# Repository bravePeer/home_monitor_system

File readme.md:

# Home Monitor System
This project idea is to gather environmental information around the home.

In principle, sensors send data to a receiver, which is connected to a server.

General flow
```
Sensor ---> Bridge ---> Server
```

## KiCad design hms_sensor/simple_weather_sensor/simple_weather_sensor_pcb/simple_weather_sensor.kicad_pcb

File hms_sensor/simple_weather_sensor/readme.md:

## Schematic of Simple Weather Sensor

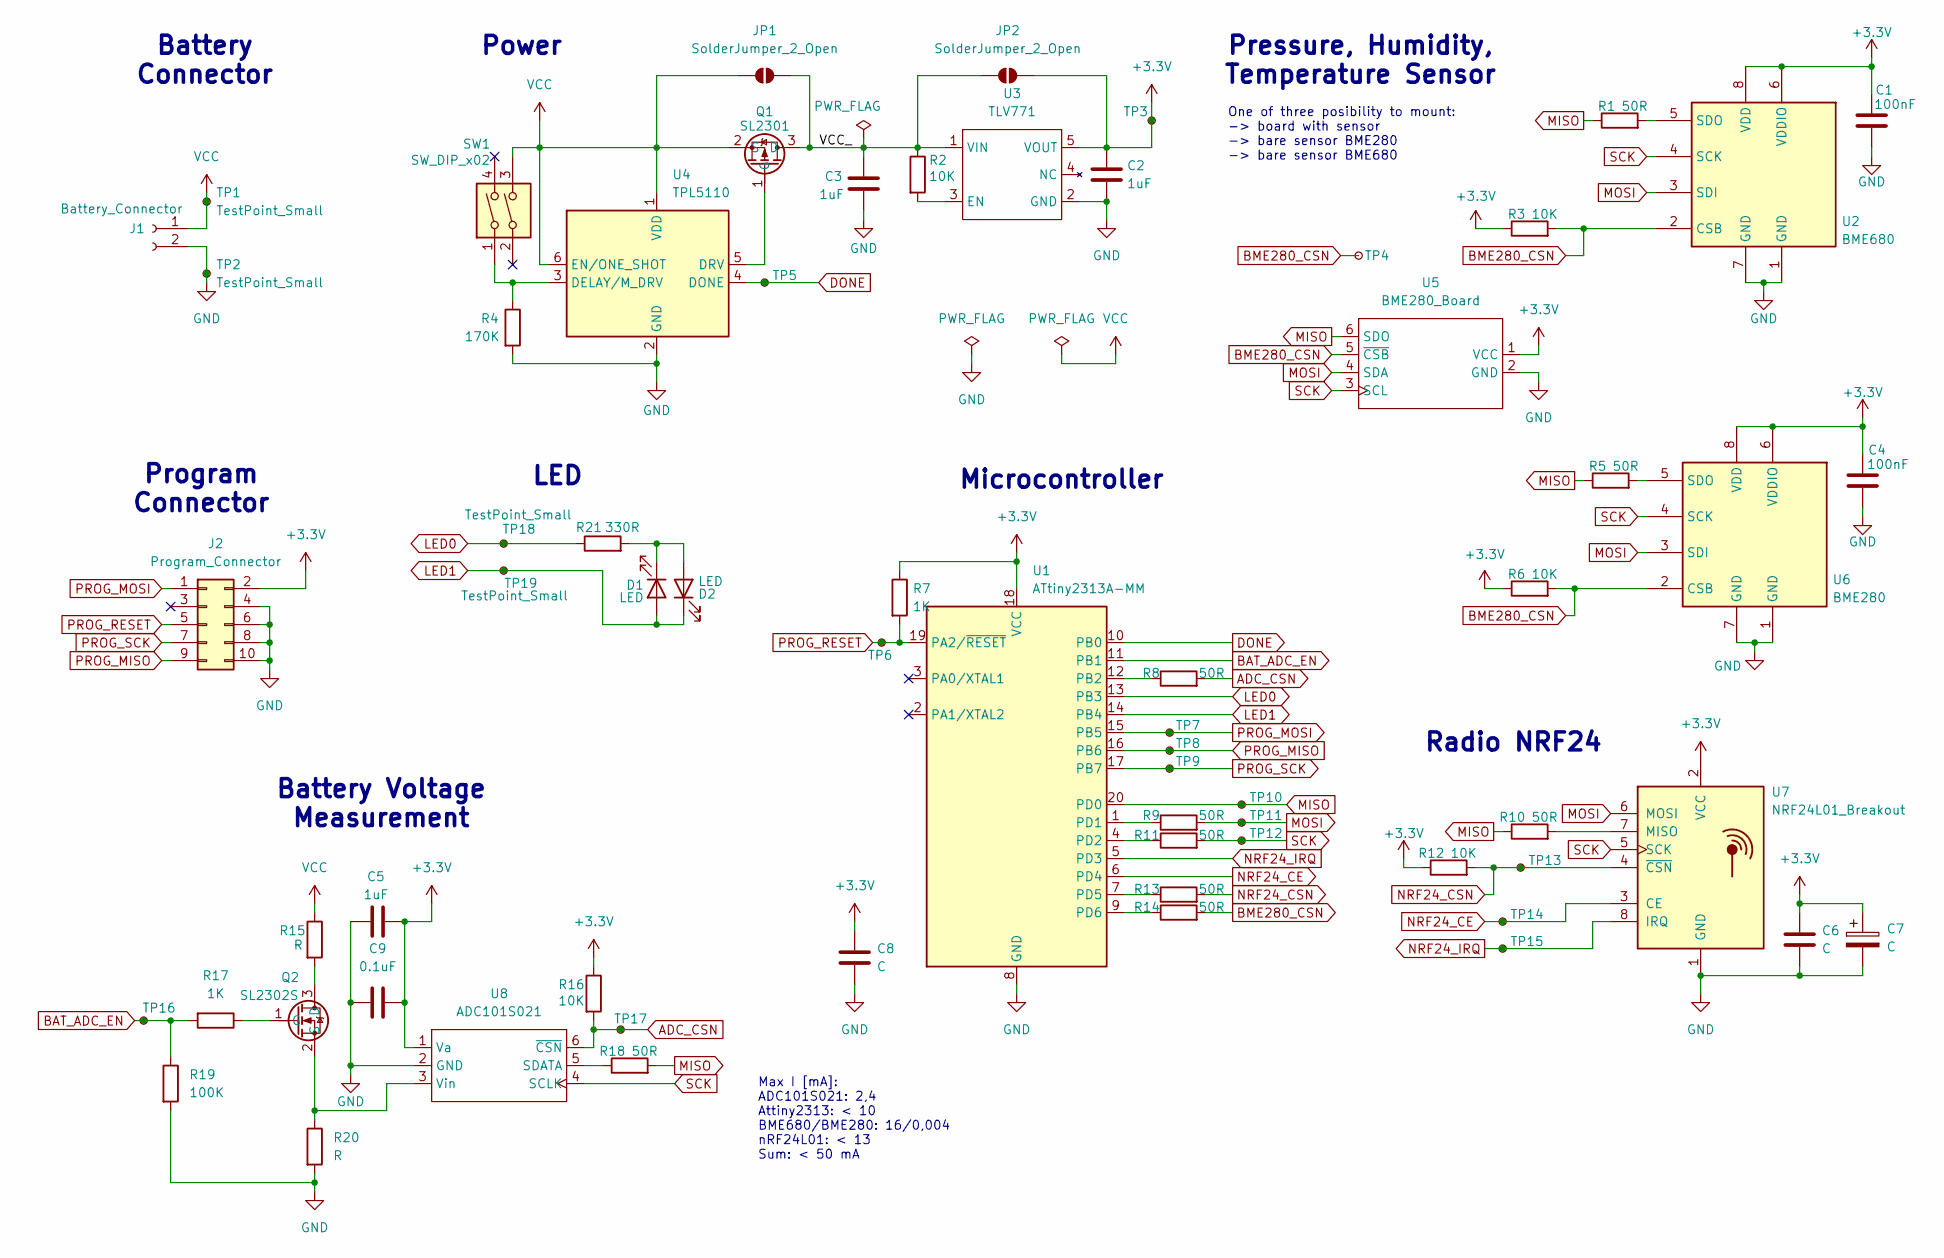
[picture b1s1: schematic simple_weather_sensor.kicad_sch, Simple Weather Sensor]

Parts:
C1, C4: 100nF; C_0805_2012Metric
C2, C3, C5: 1uF; C_0805_2012Metric
C6, C8: C; C_0805_2012Metric
C7: C; C_1210_3225Metric
C9: 0.1uF; C_0805_2012Metric
D1, D2: LED; D_0603_1608Metric
J1: Battery_Connector; PinHeader_1x02_P2.54mm_Vertical
J2: Program_Connector; PinHeader_2x05_P2.54mm_Vertical
JP1, JP2: SolderJumper_2_Open; SolderJumper-2_P1.3mm_Open_Pad1.0x1.5mm
Q1: SL2301; SOT-23
Q2: SL2302S; SOT-23
R1, R5, R8, R9, R10, R11, R13, R14, R18: 50R; R_0805_2012Metric
R2, R3, R6, R12, R16: 10K; R_0805_2012Metric
R4: 170K; R_0805_2012Metric
R7, R17: 1K; R_0805_2012Metric
R15, R20: R; R_0805_2012Metric
R19: 100K; R_0805_2012Metric
R21: 330R; R_0805_2012Metric
SW1: SW_DIP_x02; SW_Push_2P1T_Toggle_CK_PVA1xxH4xxxxxxV2
TP1, TP2, TP3, TP18, TP19: TestPoint_Small; TestPoint_Pad_D1.0mm
TP4, TP5, TP6, TP7, TP8, TP9, TP10, TP11, TP12, TP13, TP14, TP15, TP16, TP17: TestPoint_Pad_D1.0mm
U1: ATtiny2313A-MM; VQFN-20-1EP_3x3mm_P0.45mm_EP1.55x1.55mm
U2: BME680; Bosch_LGA-8_3x3mm_P0.8mm_ClockwisePinNumbering
U3: TLV771; SOT-23-5
U4: TPL5110; SOT-23-6
U5: BME280_Board; PinHeader_1x06_P2.54mm_Vertical
U6: BME280; Bosch_LGA-8_2.5x2.5mm_P0.65mm_ClockwisePinNumbering
U7: NRF24L01_Breakout; nRF24L01_Breakout
U8: ADC101S021; SOT-23-6

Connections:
+3.3V: C1.2, C2.2, C4.2, C5.1, C6.1, C7.1, C8.1, C9.2, J2.2, JP2.2 (B), R3.1, R6.1, R7.1, R12.1, R16.1, TP3.1, U1.18 (VCC), U2.6 (VDDIO), U2.8 (VDD), U3.5 (VOUT), U5.1 (VCC), U6.6 (VDDIO), U6.8 (VDD), U7.2 (VCC), U8.1 (Va)
/VCC_: C3.2, JP1.2 (B), JP2.1 (A), Q1.3 (D), R2.1, U3.1 (VIN)
ADC_CSN: R8.2, R16.2, TP17.1, U8.6 (~CSN)
BAT_ADC_EN: R17.2, R19.1, TP16.1, U1.11 (PB1)
BME280_CSN: R3.2, R6.2, R14.2, TP4.1, U2.2 (CSB), U5.5 (~CSB), U6.2 (CSB)
DONE: TP5.1, U1.10 (PB0), U4.4 (DONE)
GND: C1.1, C2.1, C3.1, C4.1, C5.2, C6.2, C7.2, C8.2, C9.1, J1.2, J2.4, J2.6, J2.8, J2.10, R4.2, R19.2, R20.2, TP2.1, U1.8 (GND), U1.21 (GND), U2.1 (GND), U2.7 (GND), U3.2 (GND), U4.2 (GND), U5.2 (GND), U6.1 (GND), U6.7 (GND), U7.1 (GND), U8.2 (GND)
LED0: R21.1, TP18.1, U1.13 (PB3)
LED1: D1.2 (A), D2.1 (K), TP19.1, U1.14 (PB4)
MISO: R1.1, R5.1, R10.1, R18.2, TP10.1, U1.20 (PD0), U5.6 (SDO)
MOSI: R9.2, TP11.1, U2.3 (SDI), U5.4 (SDA), U6.3 (SDI), U7.6 (MOSI)
NRF24_CE: TP14.1, U1.6 (PD4), U7.3 (CE)
NRF24_CSN: R12.2, R13.2, TP13.1, U7.4 (~CSN)
NRF24_IRQ: TP15.1, U1.5 (PD3), U7.8 (IRQ)
unnamed: D1.1 (K), D2.2 (A), R21.2
unnamed: Q1.1 (G), U4.5 (DRV)
unnamed: Q2.3 (D), R15.2
unnamed: Q2.1 (G), R17.1
unnamed: Q2.2 (S), R20.1, U8.3 (Vin)
unnamed: R8.1, U1.12 (PB2)
unnamed: R9.1, U1.1 (PD1)
unnamed: R11.1, U1.4 (PD2)
unnamed: R13.1, U1.7 (PD5)
unnamed: R14.1, U1.9 (PD6)
unnamed: R1.2, U2.5 (SDO)
unnamed: R2.2, U3.3 (EN)
unnamed: R4.1, SW1.1, U4.3 (DELAY/M_DRV)
unnamed: R5.2, U6.5 (SDO)
unnamed: R10.2, U7.7 (MISO)
unnamed: R18.1, U8.5 (SDATA)
PROG_MISO: J2.9, TP8.1, U1.16 (PB6)
PROG_MOSI: J2.1, TP7.1, U1.15 (PB5)
PROG_RESET: J2.5, R7.2, TP6.1, U1.19 (PA2/~RESET)
PROG_SCK: J2.7, TP9.1, U1.17 (PB7)
SCK: R11.2, TP12.1, U2.4 (SCK), U5.3 (SCL), U6.4 (SCK), U7.5 (SCK), U8.4 (SCLK)
VCC: J1.1, JP1.1 (A), Q1.2 (S), R15.1, SW1.3, TP1.1, U4.1 (VDD), U4.6 (EN/ONE_SHOT)

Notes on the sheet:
Battery Voltage Measurement
Battery Connector
Program Connector
Max I [mA]: ADC101S021: 2,4 Attiny2313: < 10 BME680/BME280: 16/0,004 nRF24L01: < 13 Sum: < 50 mA
Microcontroller
Radio NRF24
One of three posibility to mount: -> board with sensor -> bare sensor BME280 -> bare sensor BME680
Pressure, Humidity, Temperature Sensor
LED
Power

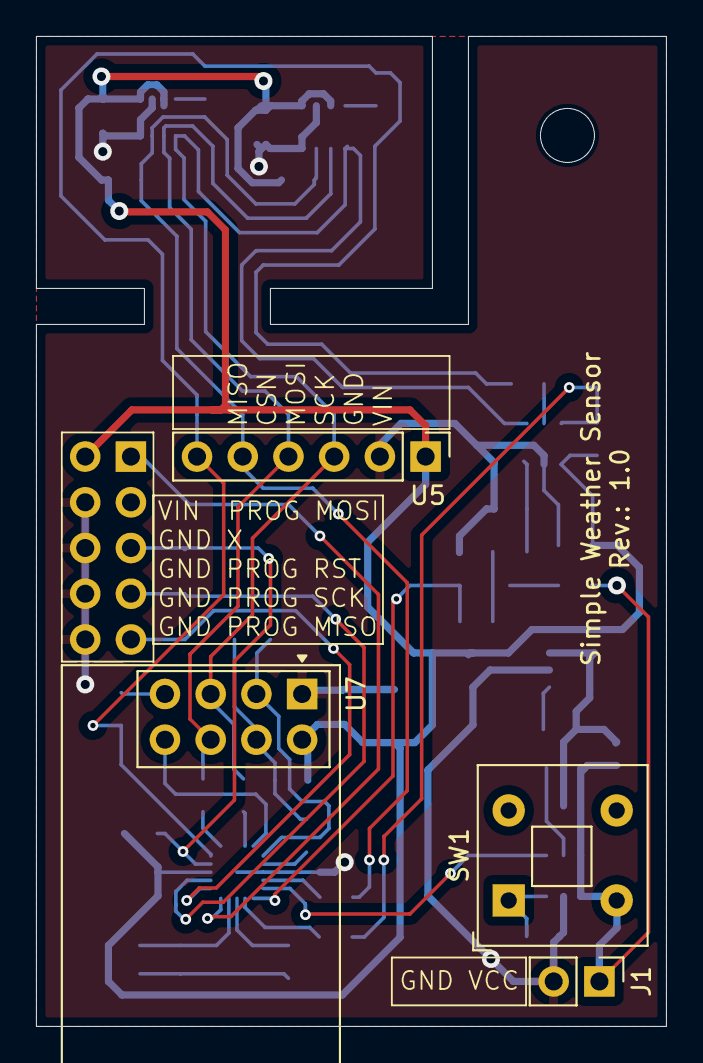
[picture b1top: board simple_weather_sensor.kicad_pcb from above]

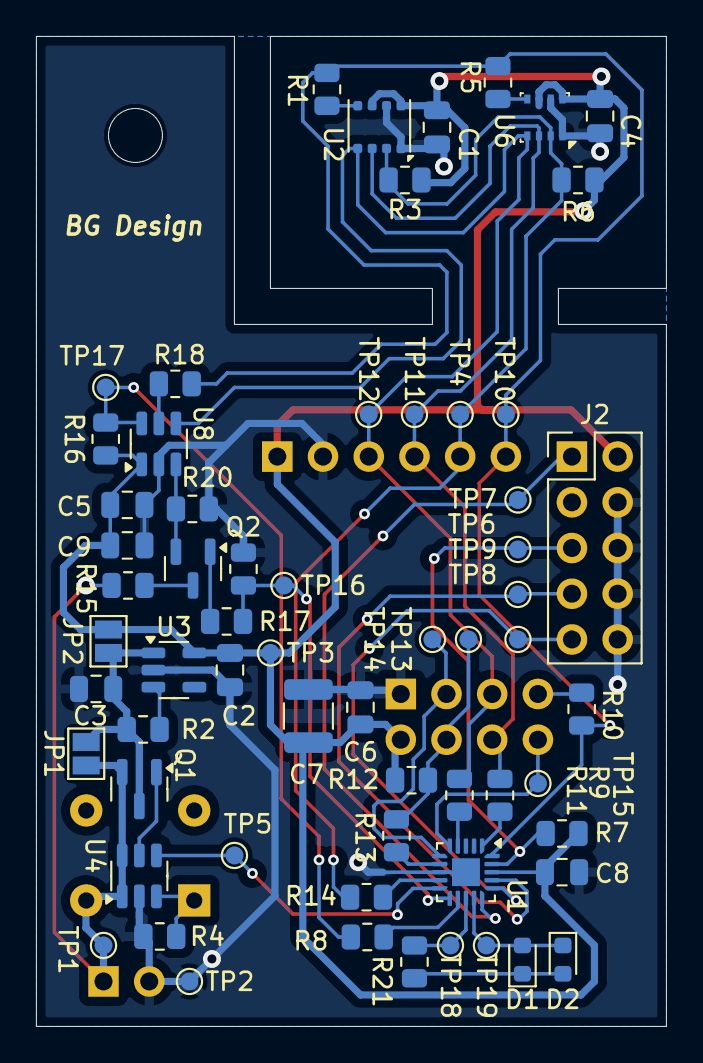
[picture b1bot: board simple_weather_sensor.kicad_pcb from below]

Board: 2 copper layers, 35.0 x 55.0 mm, 66 parts (62 on the bottom side), 36 nets.

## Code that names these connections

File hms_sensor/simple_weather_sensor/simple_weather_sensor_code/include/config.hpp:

#pragma once
#ifdef ATTINY2313A
#include <stdint.h>
extern "C"
{
    #include "avr/io.h"
    #include "avr/interrupt.h"
    #include "avr/sleep.h"
    #include "util/delay.h"
}
#include "spi.hpp"

const portType BME_CSN_PORT = &PORTD;
const pinType BME_CSN_PIN = PD6;

const portType NRF24_CSN_PORT = &PORTD;
const pinType NRF24_CSN_PIN = PD5;
inline portType NRF24_CE_PORT = &PORTD;
inline pinType NRF24_CE_PIN = PD4;
const portType NRF24_IRQ_PORT = &PORTD;
const pinType NRF24_IRQ_PIN = PD3;


const portType donePort = &PORTB;
const pinType donePin = PB0;

const portType batteryVoltageEnablePort = &PORTB;
const pinType batteryVoltageEnablePin = PB1;
const portType batteryVoltageCsnPort = &PORTB;
const pinType batteryVoltageCsnPin = PB2;

const portType ledDir = &DDRB;
const portType ledPort = &PORTB;
const pinType ledPin0 = PB4;
const pinType ledPin1 = PB3;

const portType buttonPort = &PORTB;
constexpr uint8_t buttonRightPin = PB5;
constexpr uint8_t buttonLeftPin = PB6;

constexpr pinType progMosi = PB5;
constexpr pinType progMiso = PB6;
constexpr pinType progClk = PB7;

/// @brief Initialize uC and ports
inline void init()
{
    DDRB = (1 << ledPin0) 
        | (1 << ledPin1) 
        | (1 << batteryVoltageEnablePin) 
        | (1 << batteryVoltageCsnPin)
        | (1 << donePin)
#if !defined(NO_SLEEP_TIMER)
        | (1 << progMosi)
        | (0 << progMiso)
        | (1 << progClk)
#endif
        ;

    PORTB = (1 << batteryVoltageCsnPin) 
        | (1 << ledPin0) 
        | (1 << ledPin1) 
#if defined(NO_SLEEP_TIMER)
        | (1 << buttonRightPin) 
        | (1 << buttonLeftPin)
#else
        | (1 << progMosi)
        | (0 << progMiso)
        | (1 << progClk)
#endif
        ;

    DDRD = (1 << NRF24_CSN_PIN) | (1 << NRF24_CE_PIN) | (1 << BME_CSN_PIN);
    PORTD = (1 << NRF24_CSN_PIN) | (1 << NRF24_CE_PIN) | (1 << BME_CSN_PIN);
    
    // MCUCR |= (1<<SE); // Enable sleep is set before go sleep
    MCUCR = (1 << ISC11) // Set falling edgne on INT1 (irqPin)
    | (1<<SM1) | (1<<SM0); // Configure sleep mode to Power Down
    
    // Config interrupt
    GIFR = 0xf4;
    GIMSK = (1 << INT1); // Enable INT1 interrupt

    // Disable ADC
    ACSR |= (1 << ACD);
}

#endif

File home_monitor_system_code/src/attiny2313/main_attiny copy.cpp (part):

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// }
// #include "spi.h"

// #define NRF24_CSN_PORT PORTD
// #define NRF24_CSN_PIN (uint8_t)PD4
// #define NRF24_CE_PORT PORTD
// #define NRF24_CE_PIN (uint8_t)PD5
// #define NRF24_IRQ_PORT PORTD
// #define NRF24_IRQ_PIN (uint8_t)PD3
// #define DELAY_MS(val) _delay_ms(val)
// #define DELAY_US(val) _delay_us(val)
// #include "nRF24.h"
// #define BME280_CSN_PORT PORTD
// #define BME280_CSN_PIN (uint8_t)PD6
// #include "bme280.h"
// #include "nRF24Data.h"
// // Attiny2313 -> gdy uśpione 18 uA
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

// #ifdef ATTINY2313A
// constexpr uint8_t buttonRightPin = PB0;
// constexpr uint8_t buttonLeftPin = PB1;
// constexpr uint8_t ledPIN0 = PB2;
// constexpr uint8_t ledPIN1 = PB3;
// #define LED_DDR DDRB
// #define LED_PORT PORTB

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
// void setDone()
// {
//   PORTD |= (1<<PD6);
//   _delay_ms(1);
//   PORTD &= ~(1<<PD6);
//   _delay_ms(1);
// }

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// {
//   state = State::Idle;

//   NRF24_CE_PORT &= ~(1<<NRF24_CE_PIN);
//   // _delay_us(1);
//   uint8_t status = transmitSPI(nullptr, nullptr, WriteCmd(Commands::Nop), 0, &NRF24_CSN_PORT, NRF24_CSN_PIN);
  
  
//   switch (status & SetRegister(Reg::Status::max_rt, Reg::Status::tx_ds, Reg::Status::rx_dr))
//   {
//     case SetRegister(Reg::Status::rx_dr): // Data ready, received data
//       transmitSPI(&dataCoutToProcess, &dataCoutToProcess, WriteCmd(Commands::ReadRxPayloadWidth), 1, &NRF24_CSN_PORT, NRF24_CSN_PIN);
//       // dataCoutToProcess = dataToProcess[0];
      
//       transmitSPI(dataToProcess, dataToProcess, WriteCmd(Commands::ReadRxPayload), dataCoutToProcess, &NRF24_CSN_PORT, NRF24_CSN_PIN);
//       shouldSend = 1;
//       break;
//     case SetRegister(Reg::Status::max_rt):
//       transmitSPI(nullptr, nullptr, WriteCmd(Commands::FlushTx), 0, &NRF24_CSN_PORT, NRF24_CSN_PIN);
//       turnOnRedLed();
//       break;
//     case SetRegister(Reg::Status::tx_ds):
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//   }

//   uint8_t resetReg = 0x70;
//   transmitSPI(&resetReg, &resetReg, WriteRegister(RegMap::Status), 1, &NRF24_CSN_PORT, NRF24_CSN_PIN);
//   NRF24_CE_PORT |= (1<<NRF24_CE_PIN);
// }

// volatile uint8_t timerCounter = 0;
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// int main()
// {
//   // Testing TPL
//   // DDRD |= (1<<PD6);
// //   PORTD = 0;
//   //
// //   DDRB = 0x00;
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//   //
// //   intSPI(1000u);
// //   DDRD |= (1<<csnPIN);
// //   DDRD |= (1<<PD6);
//   //
// //   PORTD |= (1<<PD6);
// //
// //   DDRD &= ~(1<<NRF24_IRQ_PIN);
// //   DDRD |= (1<<NRF24_CE_PIN);
// //   nrf24::initnRF24(); // nrf is in PRX
// //
// //   uint8_t dd = 0;
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// //   nrf24::setToPTX();
// //   uint8_t sendBuf2[5] = {'a', 'b', 'c', 'd', 'e'};
// //   nrf24::sendData(sendBuf2, 5);
// //   NRF24_CE_PORT |= (1<<NRF24_CE_PIN); 
// //   _delay_ms(5000);
// //   while (1)
// //   {
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// //         nrf24::setToPTX();
// //         uint8_t sendBuf3[5] = {'a', 'b', 'c', 'd', 'e'};
// //         nrf24::sendData(sendBuf3, 5);
// //         NRF24_CE_PORT |= (1<<NRF24_CE_PIN); 
// //         _delay_ms(500);
// //         NRF24_CE_PORT &= ~(1<<NRF24_CE_PIN); 
// //         nrf24::setToPRX();
// //         NRF24_CE_PORT |= (1<<NRF24_CE_PIN); // Receiving mode
// //         turnOnGreenLed();
// //         _delay_ms(1000);
// //         turnOffLeds();
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//   LED_DDR |= (1 << ledPIN0) | (1 << ledPIN1);
//   PORTB = (1<<buttonLeftPin) | (1<<buttonRightPin);

//   DDRD |= (1<<NRF24_CSN_PIN) | (1<<NRF24_CE_PIN);
//   NRF24_CSN_PORT |= (1<<NRF24_CSN_PIN);

//   // Config interrupt
//   MCUCR = (1<<ISC11); // Set falling edgne on INT1 (irqPin)
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//   uint8_t data = 1;
//   // uint8_t receivedBuf[5];
//   // uint8_t sendBuf[5] = {0x12, 0x23, 0x61, 0xdd, 0xab};
//   // NRF24_CE_PORT |= (1<<NRF24_CE_PIN); // Active
//   // set_sleep_mode(SLEEP_MODE_PWR_DOWN);

//   //init timer interrupt
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//   sei();
//   // Power down
//   // dd = 0;
//   // transmitSPI(&dd, &dd, ReadRegister(RegMap::Config), 1, &NRF24_CSN_PORT, NRF24_CSN_PIN);
//   // dd &= ~SetRegister(Reg::Config::pwr_up);
//   // transmitSPI(&dd, &dd, WriteRegister(RegMap::Config), 1, &NRF24_CSN_PORT, NRF24_CSN_PIN);

  

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
//       data++;
//       nrf24::setToPRX();
//       NRF24_CE_PORT |= (1<<NRF24_CE_PIN); // Receiving mode
    
//       break;    
//     }
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// #include "usart.h"

// //DDRD
// constexpr uint8_t ledPIN = PD2;
// //DDRD
// constexpr uint8_t buttonLeftPin = PD4;

// // void turnOffLeds()
// // {
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
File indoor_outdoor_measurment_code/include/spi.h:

#pragma once
#include <stdint.h>

void intSPI(uint_fast16_t baud);

template <typename T, typename K>
uint8_t simpletransmitSPI(uint8_t cData, T csPort, K csPin);

uint8_t transmitSPI_New(uint8_t* sendBuf, uint8_t* receiveBuf, uint8_t cmd, uint8_t len);

template <typename K, typename T>
uint8_t transmitSPI(uint8_t* sendBuf, uint8_t* receiveBuf, uint8_t cmd, uint8_t len, K csnPort, T csnPin)
{
  *csnPort &= (~(1<<csnPin));
  uint8_t ret = transmitSPI_New(sendBuf, receiveBuf, cmd, len);
  *csnPort |= (1<<csnPin);
  return ret;
}


#if defined(ATTINY2313A)
extern "C" 
{
  #include "avr/io.h"
  #include "util/delay.h"
}


constexpr uint8_t misoPin = PD0;
constexpr uint8_t mosiPin = PD1;
constexpr uint8_t sckPin = PD2;
constexpr uint8_t csnPIN = PD4;

// extern volatile uint8_t misoPort;
// extern volatile uint8_t csnPort;

// uint8_t simpletransmitSPI(uint8_t cData, uint8_t csPin)

inline uint8_t receiveSPIcmd(uint8_t* receiveBuf, uint8_t cmd, uint8_t len)
{
  PORTD &= ~(1<<csnPIN);
  while ( !( UCSRA & (1<<UDRE)) );/* Wait for empty transmit buffer */
  UDR = cmd;
  while ( !(UCSRA & (1<<RXC)) ); /* Wait for data to be received */
  uint8_t statusReg = UDR;

  for (uint8_t i = 0; i < len - 1; i++)
  {
    while ( !( UCSRA & (1<<UDRE)) );/* Wait for empty transmit buffer */
    UDR = 0xff;
    while ( !(UCSRA & (1<<RXC)) ); /* Wait for data to be received */
    receiveBuf[i] = UDR;
  }
  
  PORTD |= (1<<csnPIN);

  return statusReg;
}

inline uint8_t receiveSPIcmd(uint8_t* receiveBuf, uint8_t cmd, uint8_t len, volatile uint8_t csPort, uint8_t csPin)
{
  PORTD &= ~(1<<csPin);
  // csPort &= ~(1<<csPin);
  while ( !( UCSRA & (1<<UDRE)) );/* Wait for empty transmit buffer */
  UDR = cmd;
  while ( !(UCSRA & (1<<RXC)) ); /* Wait for data to be received */
  uint8_t statusReg = UDR;

  for (uint8_t i = 0; i < len - 1; i++)
  {
    while ( !( UCSRA & (1<<UDRE)) );/* Wait for empty transmit buffer */
    UDR = 0xff;
    while ( !(UCSRA & (1<<RXC)) ); /* Wait for data to be received */
    receiveBuf[i] = UDR;
  }
  
  // csPort |= (1<<csPin);
  PORTD |= (1<<csPin);

  return statusReg;
}

inline uint8_t sendSPIcmd(uint8_t* sendBuf, uint8_t cmd, uint8_t len)
{
  PORTD &= ~(1<<csnPIN);
  while ( !( UCSRA & (1<<UDRE)) );/* Wait for empty transmit buffer */
  UDR = cmd;
  while ( !(UCSRA & (1<<RXC)) ); /* Wait for data to be received */
  uint8_t statusReg = UDR;

  for (uint8_t i = 0; i < len - 1; i++)
  {
    while ( !( UCSRA & (1<<UDRE)) );/* Wait for empty transmit buffer */
    UDR = sendBuf[i];
    while ( !(UCSRA & (1<<RXC)) ); /* Wait for data to be received */
    statusReg = UDR;
  }
  
  PORTD |= (1<<csnPIN);

  return statusReg;
}

inline uint8_t sendSPIcmd(uint8_t* sendBuf, uint8_t cmd, uint8_t len, volatile uint8_t* csPort, uint8_t csPin)
{
  *csPort &= ~(1<<csPin);
  while ( !( UCSRA & (1<<UDRE)) );/* Wait for empty transmit buffer */
  UDR = cmd;
  while ( !(UCSRA & (1<<RXC)) ); /* Wait for data to be received */
  uint8_t statusReg = UDR;

  for (uint8_t i = 0; i < len - 1; i++)
  {
    while ( !( UCSRA & (1<<UDRE)) );/* Wait for empty transmit buffer */
    UDR = sendBuf[i];
    while ( !(UCSRA & (1<<RXC)) ); /* Wait for data to be received */
    statusReg = UDR;
  }
  
  *csPort |= (1<<csPin);

  return statusReg;
}



#elif defined(ATMEGA328P)
//DDRB
constexpr uint8_t misoPin = PB4;
//DDRB
constexpr uint8_t mosiPin = PB3;
//DDRB
constexpr uint8_t sckPin = PB5;
//DDRB
constexpr uint8_t csnPIN = PB2;

void initSPI()
{
  /* Set MOSI and SCK output, all others input */
  DDRB |= (1<<mosiPin)|(1<<sckPin)|(1<<csnPIN);
  DDRB &= ~(1<<misoPin);
  PORTD |= (1<<csnPIN);
  
  /* Enable SPI, Master, set clock rate fck/16 */
  SPCR = (1<<SPE)|(1<<MSTR)|(1<<SPR0);
}

void simpletransmitSPI(uint8_t data)
{
  PORTB &= ~(1<<csnPIN);
  /* Start transmission */
  SPDR = data;
  /* Wait for transmission complete */
  while(!(SPSR & (1<<SPIF)));
  PORTB |= (1<<csnPIN);
}

uint8_t transmitSPI(uint8_t* sendBuf, uint8_t* receiveBuf, uint8_t cmd, uint8_t len)
{
  //Enable
  PORTB &= ~(1<<csnPIN);

  SPDR = cmd;
  while(!(SPSR & (1<<SPIF))); /* Wait for data to be received */
  uint8_t statusReg = SPDR;

  for (uint8_t i = 0; i < len; i++)
  {
    SPDR = sendBuf[i];
    while(!(SPSR & (1<<SPIF))); /* Wait for data to be received */
    receiveBuf[i] = SPDR;
  }
  
  //Disable
  PORTB |= (1<<csnPIN);
  _delay_ms(5);
  return statusReg;
}


#endif

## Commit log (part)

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2025-02-04 Add microcontrollers code
2025-02-04 Add readme
2025-02-04 Add gitignore
2025-02-04 Remove .vscode
2025-02-05 Add list and fix native tests
2025-02-06 Update list and add sensor tests
2025-02-06 Add PC app
2025-02-28 Change folder name
2025-02-28 Add schematic to Simple Weather Sensor
2025-03-09 Clean up and update attiny sensor code
2025-03-09 Fix packet len in attiny sensor and remove unnecessary filse
2025-03-18 Add sensor files and commands to debug
2025-03-22 Add reading sensor temperature and pressure
2025-03-22 Split to diffrent files
2025-05-28 Add simple deamon, add docker compose and move files
2025-06-02 Add sensor_menager and update deamon
2025-06-02 Refactor code structure for improved readability and maintainability
2025-06-14 Attiny2313: Add data in EEPROM and split code into files
2025-06-14 Remove Atmega328p and modify Attiny2313A config
2025-06-14 Change send delay and remove blink info
2025-07-21 Update BME lib
2025-07-21 Add check connection to nrf24 lib
2025-07-21 Move files and update
2025-07-24 Add work done
2025-07-24 Change packet structure and add packet types
2025-07-24 Update Attiny2313 config and add work done and battery voltage
